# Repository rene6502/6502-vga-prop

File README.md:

# 6502-vga-prop

This project realizes a VGA card, which can be connected to the expansion port of the [6502-cent1](https://github.com/rene6502/6502-cent1).

Features:
-	VGA Signal 640 x 480 @ 60 Hz Industry standard timing
-	Display resolution 320x240 pixels, 40x30 characters, 16 out of 64 colors
-	Single graphics mode using tiles and user-definable character set
-	Integrated funscii system font (2 colors)
-	256 user-defined characters (8x8 pixels, 16 colors) in addition to the system font
-	Memory interface to 6502 bus via 16K dual-port static video RAM (VRAM)
-	Support for double buffering
-	VGA driver extensible by Propeller assembly language

## Hardware

The video signal is generated by a Parallax Propeller 1 using 8 GPIO pins to create a 2-bit RGB, a vertical and a horizontal synch signal.  
The Propeller stores the program in an eeprom and can be programmed via the serial interface.  
Because the Propeller operates at 3.3V a regulator and level shifters are integrated.  
To overcome the limitation of Propeller GPIO pins a binary counter is used to generate the address to the VRAM.  
The 6502 interfaces directly with the VRAM. The 6502 will interact with the VGA via memory, like the old video chips of the 8-bit home-computers.  

## Examples

### Hello,World!
Source: [hello-world.asm](demo/hello-world.asm)  

### Demo 
Display colorized texts and demonstrates usage of the user-defined character set.  
Source: [vga_demo.asm](demo/vga_demo.asm)  

## Software
The software consists of the vga driver, which is written in Propeller assembly language.  
It makes use of the 320x240 [scanline driver](https://github.com/konimaru/waitvid.2048) from Marko Lukat which uses a single cog.  
6 renderer cogs are used to convert the tilemap into scanlines using the addressed character set.  
A separate vram driver cog is used to read the VRAM memory and copy it to the hub memory, where it can be accessed from the renderer cogs.  
The vram driver copies from VRAM to a separate copy buffer.  
The 6502 can control when and what part of this copy buffer will be transferred to the main hub memory, where it will be read from the renderer cogs (double buffering).  
This copy is done during the vertical blank so that the rendering will not be disturbed by changing the VRAM memory from the 6502.  
The 6502 can control when and what parts should be copied.

**Memory Map**
| area     | start | end  | description        |
| -------- | ----- | ---- | ------------------ |
| ctrl_cmd | 0200  | 0200 | command            |
| tilemap  | 0210  | 0B6F | screen tiles       |
| palettes | 0B70  | 0C6F | color palettes     |
| frame    | 0C70  | 0C71 | frame number       |
| charset  | 0C80  | 2C7F | user character set |

**ctrl_cmd**  
This register controls which memory will be transferred during the next vertical blank  
bit 0: copy control section  
bit 1: copy tilemap and palettes  
bit 2: copy user-defined character set

**tilemap**  
screen tiles with 40 columns and 30 rows, starting with first row  
each tile is 16 bit, LSB contains the character code and MSB the palette index  
if the bit 4 of the MSB is set to 1 then the user-defined character set is used, otherwise the system character set  

**palettes**  
Table of 16 palettes, each containing 16 colors  
Color is encoded as bit 6-7: R, bit 4-5: G, bit 2-3 B, bit 0-1 always 0  
The system characters use 2 colors, the user-defined characters use 16 colors  

**frame**  
16 bit frame counter, this value is incremented after the buffer was copied during the vertical blank

## Implementation details

### Tilemap and memory map

### Timing

## Schematics and PCB
- [PDF](doc/schematics.pdf) of schematics
- See the KiCad project in folder [kicad](./kicad)  

## Connecting vga board with 6502-cent1
The vga board is connected using a 32-pin ribbon IDC cable. The RAM from the mainboard must be removed.  
It is replaced by the 16k VRAM of the vga board using the address space $0000-$3FFF.  

## Connect serial to program Parallax Propeller
Initially the Propeller must be programmed with the VGA driver.
To do so a USB-Serial Adapter is required.  
It must provide a DTR signal, which is needed to start the Propeller boot-loading process.  
A working example is [FT232-AZ USB to TTL Serial Adapter for 3.3V and 5V](https://www.az-delivery.de/en/products/ftdi-adapter-ft232rl).  
The spin/assembly program can be compiled and loaded to the eeprom using the [SimpleIDE Software from Parallax](https://www.parallax.com/download/Propeller-1-software).  

Once loaded the vga will show a simple startup screen and is ready to display the tile map.

## Credits
-	Wuerfel21 for the [Funscii font](https://github.com/Wuerfel21/funscii)
-	Marko Lukat for the [scanline video driver](https://github.com/konimaru/waitvid.2048)
- Adam Saltsman for the ["1985" tileset](https://adamatomic.itch.io/1985)

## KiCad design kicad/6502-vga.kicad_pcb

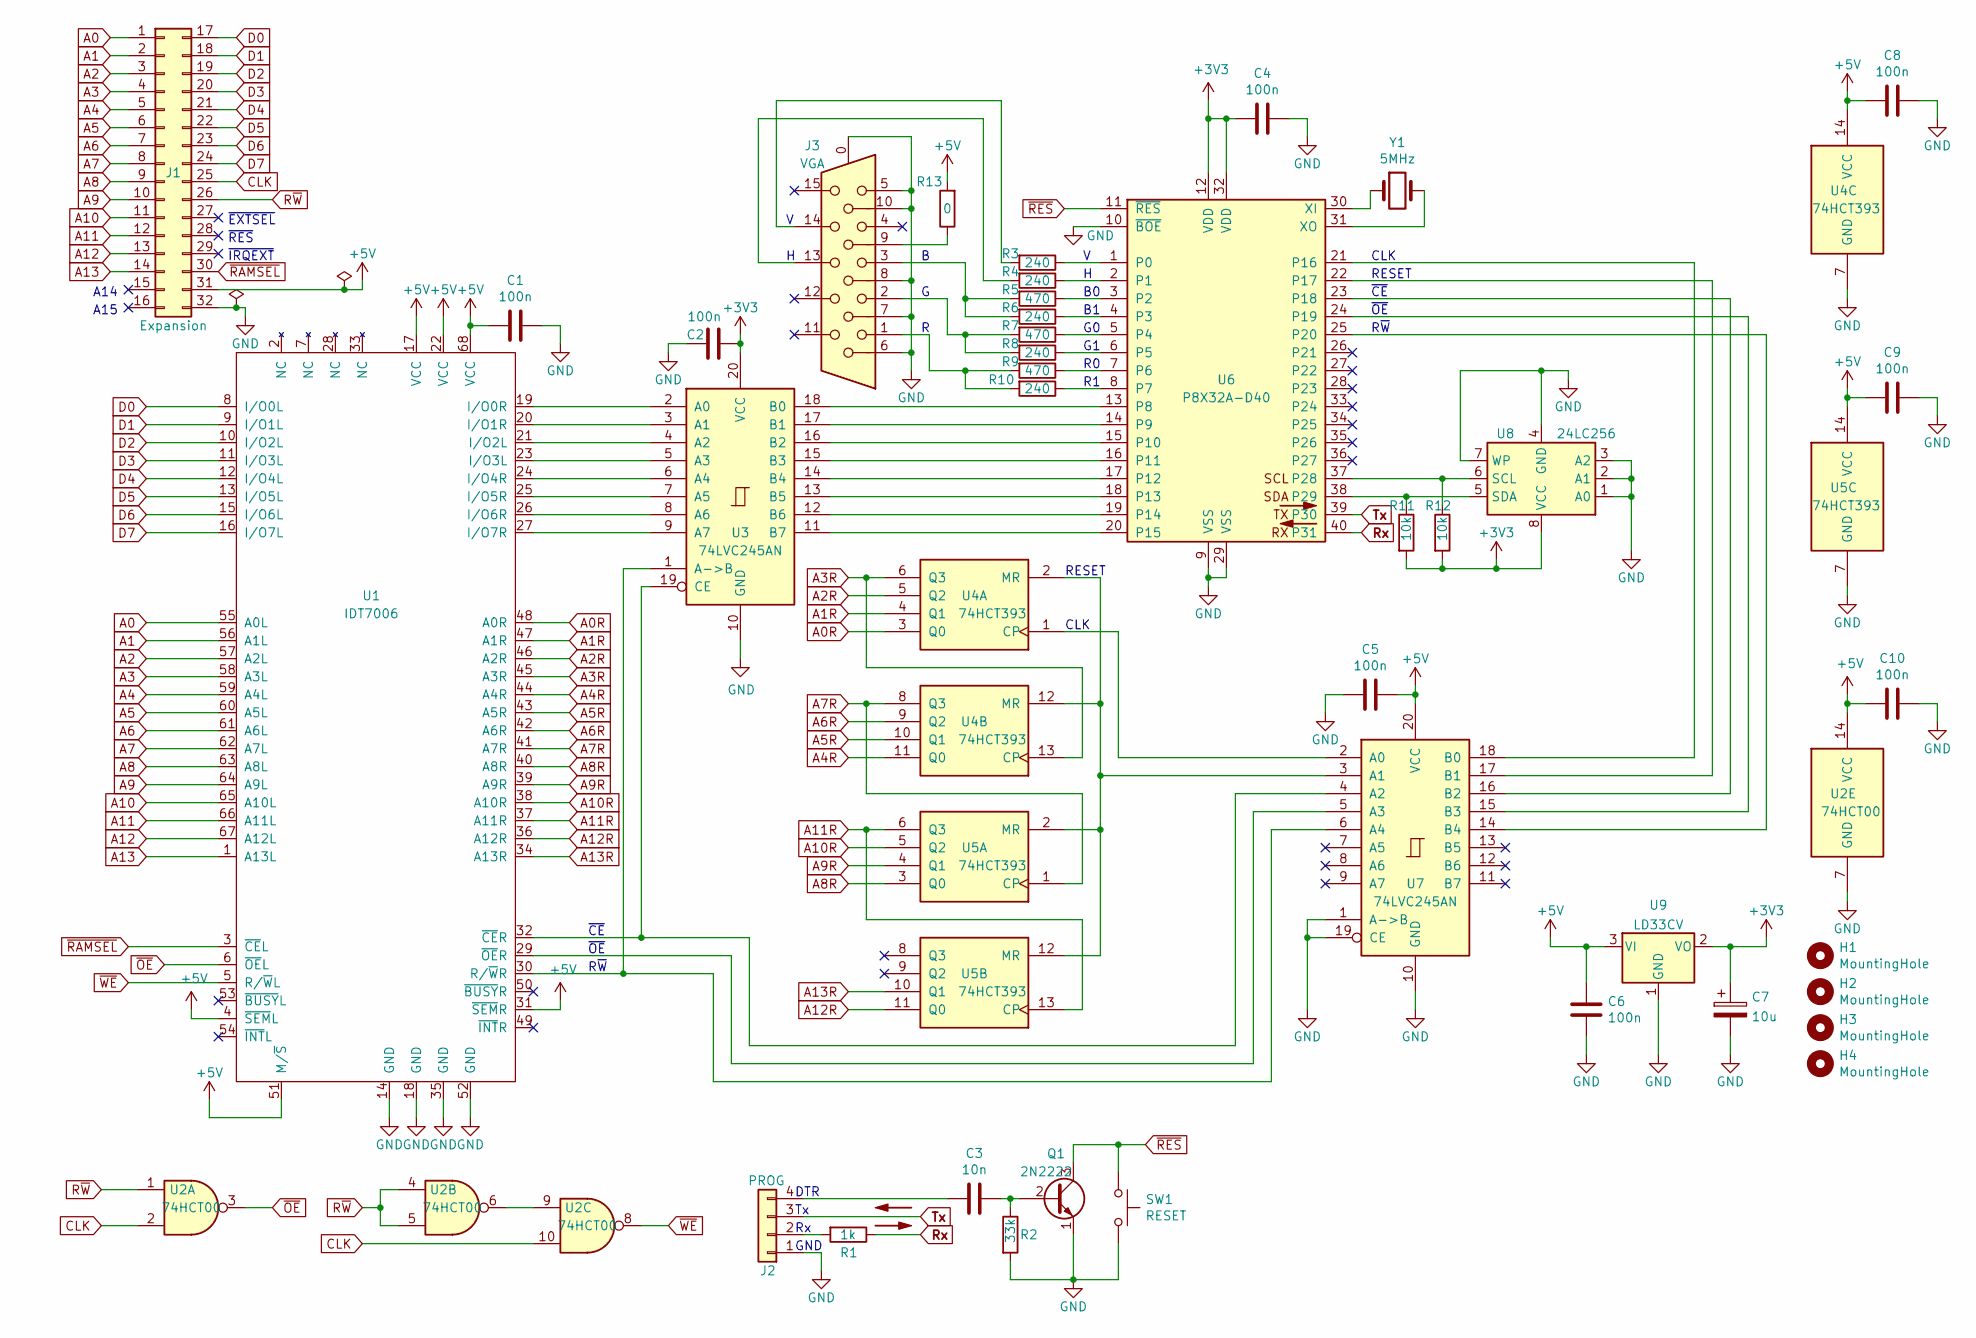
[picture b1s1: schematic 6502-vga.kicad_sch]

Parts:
C1, C2, C4, C5, C6, C8, C9, C10: 100n; C_Disc_D5.0mm_W2.5mm_P5.00mm
C3: 10n; C_Disc_D5.0mm_W2.5mm_P5.00mm
C7: 10u; CP_Radial_D5.0mm_P2.00mm
H1, H2, H3, H4: MountingHole; MountingHole_3.2mm_M3_Pad_Via
J1: Expansion; PinSocket_2x16_P2.54mm_Vertical
J2: PROG; PinSocket_1x04_P2.54mm_Vertical
J3: VGA; DSUB-15-HD_Female_Horizontal_P2.29x1.98mm_EdgePinOffset8.35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
Q1: 2N2222; TO-92
R1: 1k; R_Axial_DIN0207_L6.3mm_D2.5mm_P10.16mm_Horizontal
R2: 33k; R_Axial_DIN0207_L6.3mm_D2.5mm_P10.16mm_Horizontal
R3, R4, R6, R8, R10: 240; R_Axial_DIN0207_L6.3mm_D2.5mm_P10.16mm_Horizontal
R5, R7, R9: 470; R_Axial_DIN0207_L6.3mm_D2.5mm_P10.16mm_Horizontal
R11, R12: 10k; R_Axial_DIN0207_L6.3mm_D2.5mm_P10.16mm_Horizontal
R13: 0; R_Axial_DIN0207_L6.3mm_D2.5mm_P10.16mm_Horizontal
SW1: RESET; SW_PUSH_6mm_H4.3mm
U1: IDT7006; PLCC-68_THT-Socket
U2: 74HCT00; DIP-14_W7.62mm_LongPads
U3, U7: 74LVC245AN; DIP-20_W7.62mm_LongPads
U4, U5: 74HCT393; DIP-14_W7.62mm_LongPads
U6: P8X32A-D40; DIP-40_W15.24mm_LongPads
U8: 24LC256; DIP-8_W7.62mm_Socket_LongPads
U9: LD33CV; TO-220-3_Horizontal_TabDown
Y1: 5MHz; Crystal_HC49-U_Vertical

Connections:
+3V3: C2.1, C4.2, C7.1, R11.2, R12.2, U3.20 (VCC), U6.12 (VDD), U6.32 (VDD), U8.8 (VCC), U9.2 (VO)
+5V: C1.2, C5.1, C6.1, C8.2, C9.2, C10.2, J1.31, R13.2, U1.4 (~SEML), U1.17 (VCC), U1.22 (VCC), U1.31 (~SEMR), U1.51 (M/~S), U1.68 (VCC), U2.14 (VCC), U4.14 (VCC), U5.14 (VCC), U7.20 (VCC), U9.3 (VI)
A0: J1.1, U1.55 (A0L)
A0R: U1.48 (A0R), U4.3 (Q0)
A1: J1.2, U1.56 (A1L)
A1R: U1.47 (A1R), U4.4 (Q1)
A2: J1.3, U1.57 (A2L)
A2R: U1.46 (A2R), U4.5 (Q2)
A3: J1.4, U1.58 (A3L)
A3R: U1.45 (A3R), U4.6 (Q3), U4.13 (CP)
A4: J1.5, U1.59 (A4L)
A4R: U1.44 (A4R), U4.11 (Q0)
A5: J1.6, U1.60 (A5L)
A5R: U1.43 (A5R), U4.10 (Q1)
A6: J1.7, U1.61 (A6L)
A6R: U1.42 (A6R), U4.9 (Q2)
A7: J1.8, U1.62 (A7L)
A7R: U1.41 (A7R), U4.8 (Q3), U5.1 (CP)
A8: J1.9, U1.63 (A8L)
A8R: U1.40 (A8R), U5.3 (Q0)
A9: J1.10, U1.64 (A9L)
A9R: U1.39 (A9R), U5.4 (Q1)
A10: J1.11, U1.65 (A10L)
A10R: U1.38 (A10R), U5.5 (Q2)
A11: J1.12, U1.66 (A11L)
A11R: U1.37 (A11R), U5.6 (Q3), U5.13 (CP)
A12: J1.13, U1.67 (A12L)
A12R: U1.36 (A12R), U5.11 (Q0)
A13: J1.14, U1.1 (A13L)
A13R: U1.34 (A13R), U5.10 (Q1)
CLK: J1.25, U2.2, U2.10
D0: J1.17, U1.8 (I/O0L)
D1: J1.18, U1.9 (I/O1L)
D2: J1.19, U1.10 (I/O2L)
D3: J1.20, U1.11 (I/O3L)
D4: J1.21, U1.12 (I/O4L)
D5: J1.22, U1.13 (I/O5L)
D6: J1.23, U1.15 (I/O6L)
D7: J1.24, U1.16 (I/O7L)
GND: C1.1, C2.2, C4.1, C5.2, C6.2, C7.2, C8.1, C9.1, C10.1, J1.32, J2.1, J3.0, J3.5, J3.6, J3.7, J3.8, J3.10, Q1.1 (E), R2.2, SW1.2, U1.14 (GND), U1.18 (GND), U1.35 (GND), U1.52 (GND), U2.7 (GND), U3.10 (GND), U4.7 (GND), U5.7 (GND), U6.9 (VSS), U6.10 (~BOE), U6.29 (VSS), U7.1 (A->B), U7.10 (GND), U7.19 (CE), U8.1 (A0), U8.2 (A1), U8.3 (A2), U8.4 (GND), U8.7 (WP), U9.1 (GND)
unnamed: C3.1, Q1.2 (B), R2.1
unnamed: C3.2, J2.4
unnamed: J2.2, R1.2
unnamed: J3.1, R9.2, R10.2
unnamed: J3.2, R7.2, R8.2
unnamed: J3.3, R5.2, R6.2
unnamed: J3.9, R13.1
unnamed: J3.13, R4.2
unnamed: J3.14, R3.2
unnamed: R3.1, U6.1 (P0)
unnamed: R4.1, U6.2 (P1)
unnamed: R5.1, U6.3 (P2)
unnamed: R6.1, U6.4 (P3)
unnamed: R7.1, U6.5 (P4)
unnamed: R8.1, U6.6 (P5)
unnamed: R9.1, U6.7 (P6)
unnamed: R10.1, U6.8 (P7)
unnamed: R11.1, U6.38 (P29), U8.5 (SDA)
unnamed: R12.1, U6.37 (P28), U8.6 (SCL)
unnamed: U1.19 (I/O0R), U3.2 (A0)
unnamed: U1.20 (I/O1R), U3.3 (A1)
unnamed: U1.21 (I/O2L), U3.4 (A2)
unnamed: U1.23 (I/O3L), U3.5 (A3)
unnamed: U1.24 (I/O4R), U3.6 (A4)
unnamed: U1.25 (I/O5R), U3.7 (A5)
unnamed: U1.26 (I/O6R), U3.8 (A6)
unnamed: U1.27 (I/O7R), U3.9 (A7)
unnamed: U1.29 (~OER), U7.5 (A3)
unnamed: U1.30 (R/~WR), U3.1 (A->B), U7.6 (A4)
unnamed: U1.32 (~CER), U3.19 (CE), U7.4 (A2)
unnamed: U2.6, U2.9
unnamed: U3.11 (B7), U6.20 (P15)
unnamed: U3.12 (B6), U6.19 (P14)
unnamed: U3.13 (B5), U6.18 (P13)
unnamed: U3.14 (B4), U6.17 (P12)
unnamed: U3.15 (B3), U6.16 (P11)
unnamed: U3.16 (B2), U6.15 (P10)
unnamed: U3.17 (B1), U6.14 (P9)
unnamed: U3.18 (B0), U6.13 (P8)
unnamed: U4.1 (CP), U7.2 (A0)
unnamed: U4.2 (MR), U4.12 (MR), U5.2 (MR), U5.12 (MR), U7.3 (A1)
unnamed: U6.21 (P16), U7.18 (B0)
unnamed: U6.22 (P17), U7.17 (B1)
unnamed: U6.23 (P18), U7.16 (B2)
unnamed: U6.24 (P19), U7.15 (B3)
unnamed: U6.25 (P20), U7.14 (B4)
unnamed: U6.30 (XI), Y1.1
unnamed: U6.31 (XO), Y1.2
Rx: R1.1, U6.40 (P31)
R~W: J1.26, U2.1, U2.4, U2.5
Tx: J2.3, U6.39 (P30)
~OE: U1.6 (~OEL), U2.3
~RAMSEL: J1.30, U1.3 (~CEL)
~RES: Q1.3 (C), SW1.1, U6.11 (~RES)
~WE: U1.5 (R/~WL), U2.8

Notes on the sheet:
~{EXTSEL}
R~{W}
RESET
GND
~{RES}
A15
~{CE}
~{OE}
~{IRQEXT}
CLK
A14
DTR

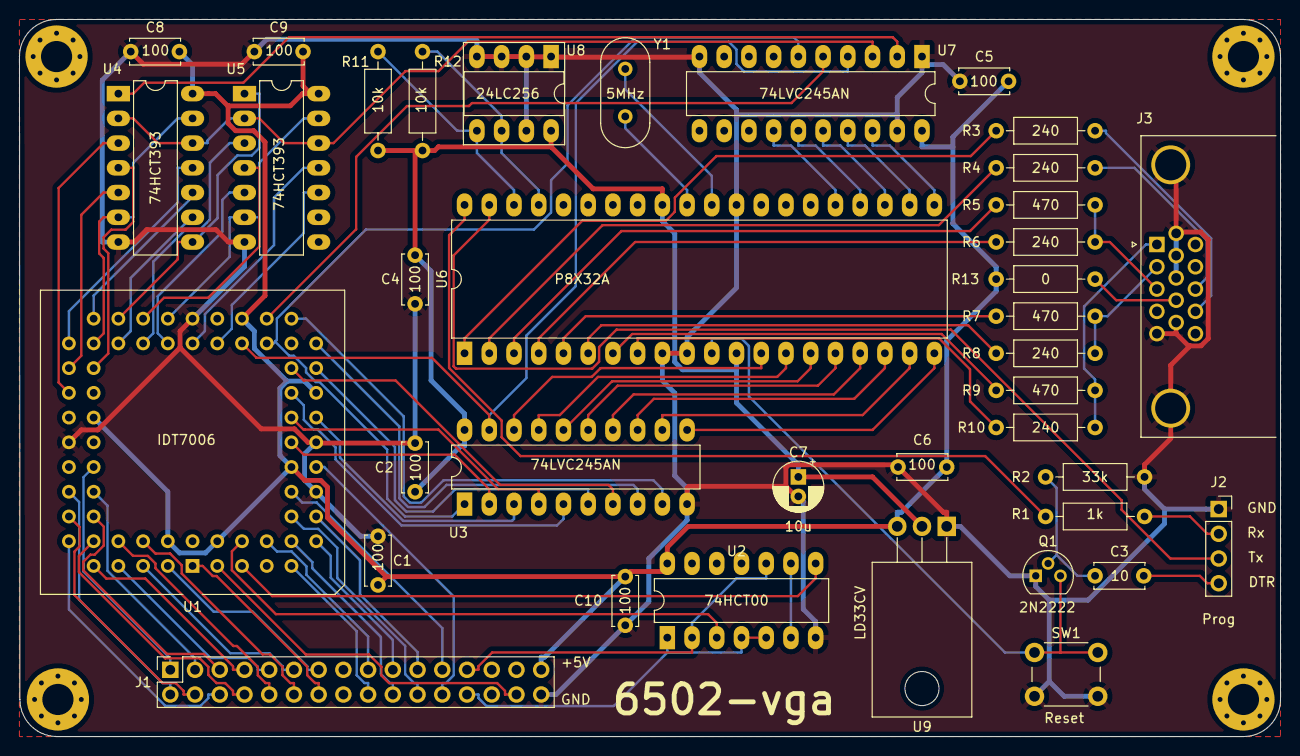
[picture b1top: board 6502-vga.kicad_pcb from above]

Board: 2 copper layers, 129.5 x 73.7 mm, 42 parts (0 on the bottom side), 95 nets.
